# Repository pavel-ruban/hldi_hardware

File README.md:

# hldi_hardware

This is code for STM32f103 based PCB which implement home laser for home PCB manufacturing, it use ultra violet laser to make photoresis method done PCBs

Basically it's CNC machine which currently has 2 variants:
1. x axis stepper motor + y axis DC brushed motor with optical encoder line from PC printer
2. 2 axes are done with DC brushed motors kinematic is corexy 

Caution: This is currently in raw alpha & not fully working

GUI for this stuff can be found in sibling repository: https://github.com/pavel-ruban/hldi_gui

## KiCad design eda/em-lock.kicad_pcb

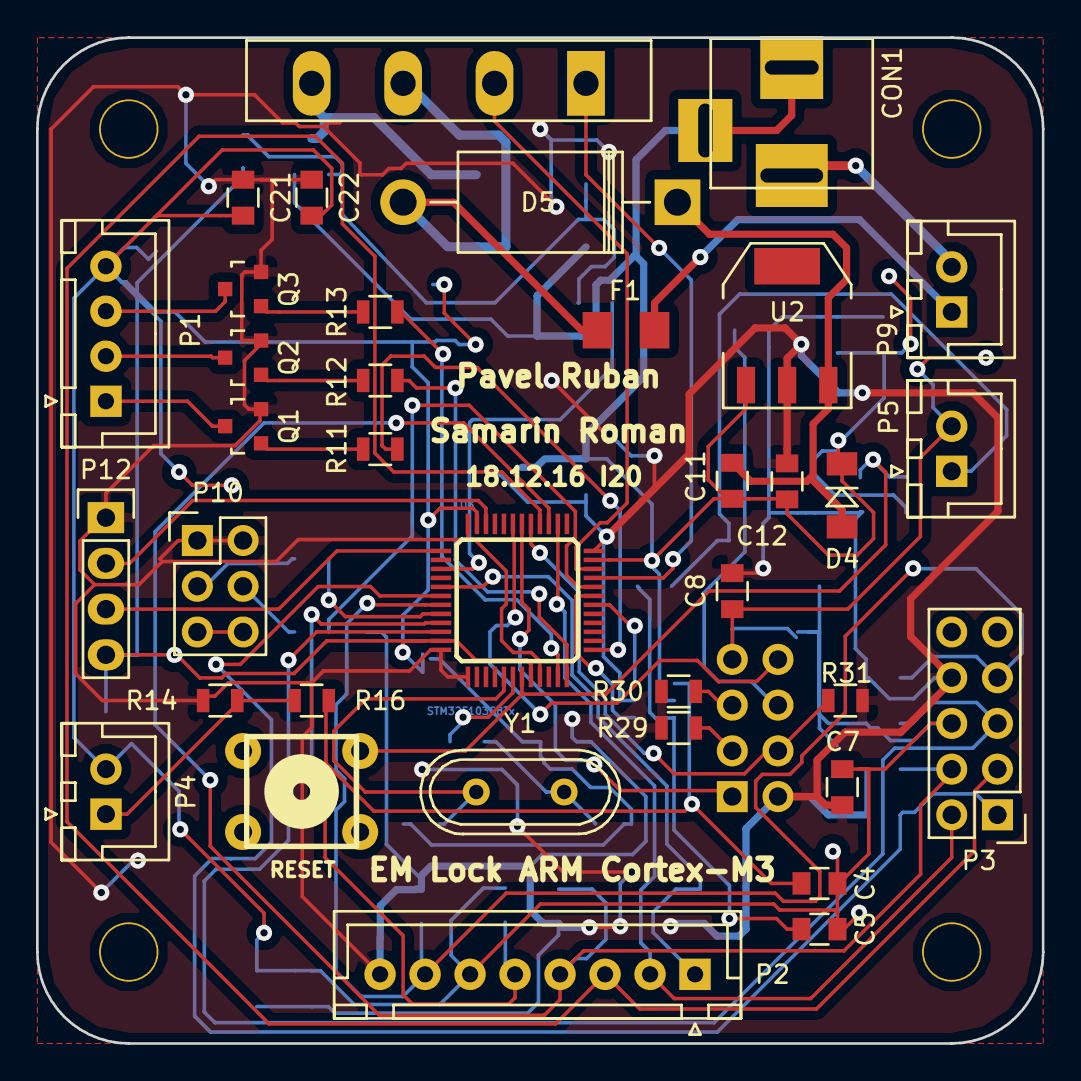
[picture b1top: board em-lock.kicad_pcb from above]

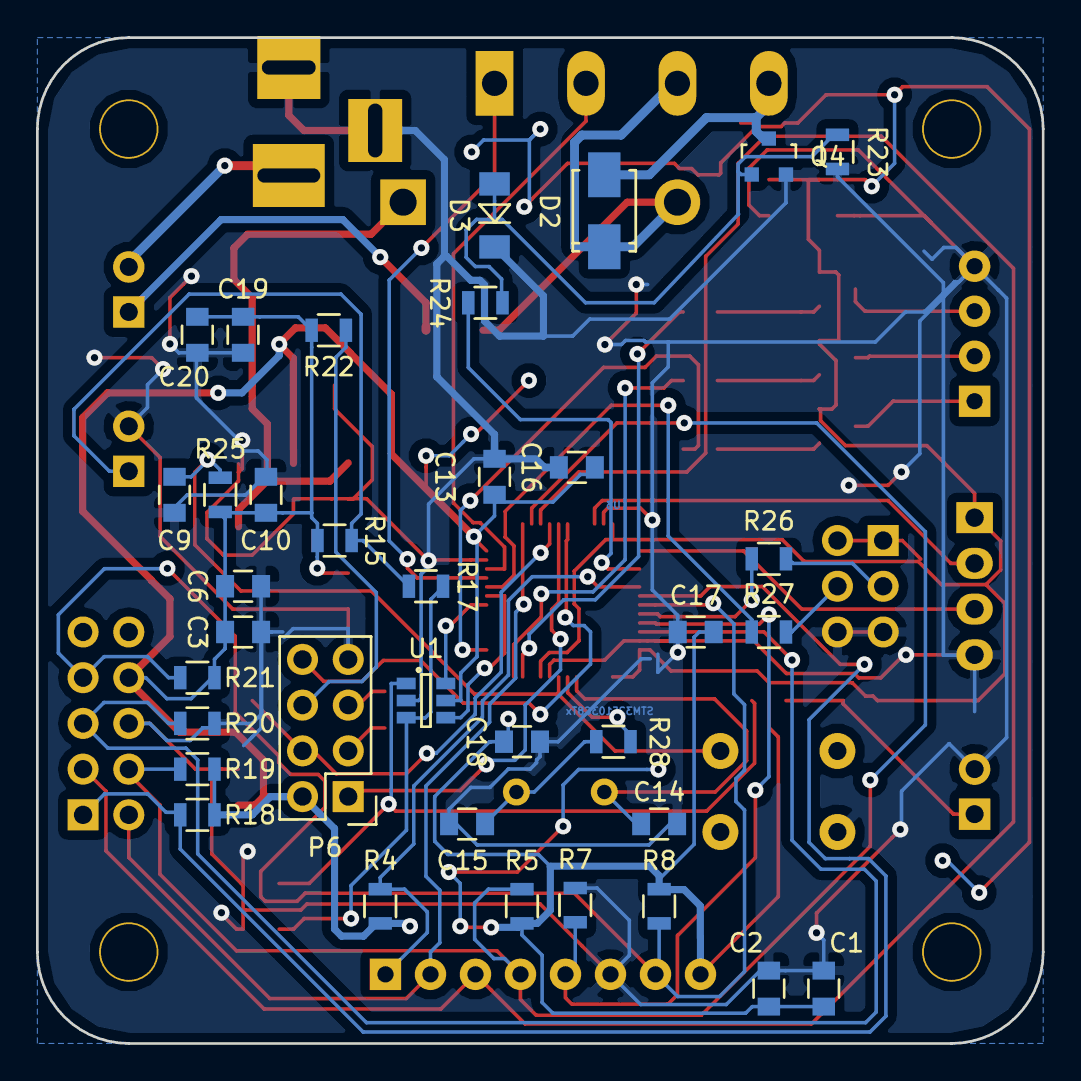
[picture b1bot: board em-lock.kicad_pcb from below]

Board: 2 copper layers, 55.9 x 55.9 mm, 78 parts (36 on the bottom side), 50 nets.

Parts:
C1, C3, C7, C9, C10, C13, C16, C17, C18, C22: 100nF; C_0805
C2, C6, C8, C11, C19, C21: 10uF; C_0805
C4, C5: 0; C_0805
C12: 22uF; C_0805
C14, C15: 2pF; C_0805
C20: 1uF; C_0805
CON1: BARREL_JACK; DC-005
D2: M7; SMA_Standard
D3: ZENER-MOSFET-GATE; MiniMELF_Standard
D4: LDO-12V; MiniMELF_Standard
D5: 0; Diode_DO-201AD_Horizontal_RM15
F1: 3A; Fuse_SMD1206_Wave
H1, H2, H3, H4: MountingHole_3.1mm
H8, H9: MountingHole_1.9mm
P1: EXT_LED_CONN; JST_XH_B04B-XH-A_04x2.50mm_Straight
P2: RC522A; JST_XH_B08B-XH-A_08x2.50mm_Straight
P3: RC522B; Pin_Header_Straight_2x05
P4: BTN_OPEN; JST_XH_B02B-XH-A_02x2.50mm_Straight
P5: BTN_CALL; JST_XH_B02B-XH-A_02x2.50mm_Straight
P6: ESP8266_CONN; ESP8266
P7: LOCK_CONN; PhoenixContact_MSTBA-G_04x5.08mm_Angled
P9: PWR_SW_CONN; JST_XH_B02B-XH-A_02x2.50mm_Straight
P10: BOOT_SEL_CONN; Pin_Header_Straight_2x03
P12: SWD_CONN; Pin_Header_Straight_1x04
Q1, Q2, Q3: MMBT3906; SOT-23
Q4: MOSFET-NCHANNELSMD; SOT-23
R4, R5, R7, R8, R18, R19, R20, R21, R22, R29, R30, R31: 4.7k; R_0805
R11, R12, R13: 2k; R_0805
R14, R15, R23, R25, R26, R27: 10k; R_0805
R16, R17: 0; R_0805
R24: 240; R_0805
R28: 0R; R_0805
RESET: RST_BTN; PCB_PUSH
U1: 74LVC2G14; SOT-23-6
U2: LD1117S33CTR; SOT-223
U3: STM32F103C8Tx; SparkFun-LQFP-48
Y1: 8MHz; Crystal_HC49-U_Vertical

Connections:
/stm32f103c8/12V_EXT: CON1.1, P9.2
/stm32f103c8/BOOT0: R26.1, U3.44
/stm32f103c8/LDO_IN: C11.1, D4.1, D5.1, U2.3
/stm32f103c8/NRST: C9.1, R25.1, RESET.2, U3.7
/stm32f103c8/PB2/BOOT1: R27.1, U3.20
/stm32f103c8/PD0/RCC_OSC_IN: C14.1, U3.5, Y1.1
/stm32f103c8/PD1/RCC_OSC_OUT: R28.1, U3.6
/stm32f103c8/SWCLK: P12.3, U3.37
/stm32f103c8/SWDIO: P12.2, U3.34
BTN_CALL: U1.4, U3.19
BTN_OPEN: U1.6, U3.18
EM_LOCK: D2.1, D5.2, F1.1, P7.3
ESP_RESET: P6.4, R31.2, U3.29
GND: C1.2, C2.2, C3.2, C4.1, C5.1, C6.2, C7.1, C8.1, C9.2, C10.2, C11.2, C12.2, C13.1, C14.2, C15.2, C16.2, C17.2, C18.2, C19.1, C20.1, C21.2, C22.2, CON1.2, CON1.3, D3.2, D4.2, P1.4, P2.6, P3.6, P4.2, P5.2, P6.7, P10.5, P10.6, P12.4, Q4.2, R7.1, R20.1, R23.2, RESET.1, U1.2, U2.1, U3.8, U3.23, U3.35, U3.47
LOCK_GND: D2.2, P7.4, Q4.3
LOCK_OPEN: R24.1, U3.39
unnamed: C4.2, R16.1, U1.1
unnamed: C5.2, R17.1, U1.3
unnamed: C15.1, R28.2, Y1.2
unnamed: D3.1, Q4.1, R23.1, R24.2
unnamed: F1.2, P9.1
unnamed: P4.1, R14.2, R16.2
unnamed: P5.1, R15.2, R17.2
unnamed: P6.3, R29.1
unnamed: P6.5, R30.1
unnamed: P6.6, R22.2
unnamed: P10.3, R26.2
unnamed: P10.4, R27.2
unnamed: Q1.1, R11.1
unnamed: Q2.1, R12.1
unnamed: Q3.1, R13.1
OUT_BLUE: P1.1, Q1.3
OUT_GREEN: P1.2, Q2.3
OUT_RED: P1.3, Q3.3
PB5_RC522A_CS: P2.1, R4.2, U3.41
PB6_RC522B_CS: P3.1, R18.2, U3.42
PB7_RC522_RST: P2.7, P3.7, R8.2, R21.2, U3.43
PB8_RC522A_IRQ: P2.5, R7.2, U3.45
PB9_RC522B_IRQ: P3.5, R20.2, U3.46
PB13_SPI2_SCK: P2.2, P3.2, U3.26
PB14_SPI2_MISO: P2.4, P3.4, R5.2, R19.2, U3.27
PB15_SPI2_MOSI: P2.3, P3.3, U3.28
PIN_BLUE: R11.2, U3.13
PIN_GREEN: R12.2, U3.12
PIN_RED: R13.2, U3.11
UART_EXT_RX: P7.2, U3.22
UART_EXT_TX: P7.1, U3.21
UART_INT_RX: P6.8, U3.31
UART_INT_TX: P6.1, U3.30
VCC: C1.1, C2.1, C3.1, C6.1, C7.2, C8.2, C10.1, C12.1, C13.2, C16.1, C17.1, C18.1, C19.2, C20.2, C21.1, C22.1, P2.8, P3.8, P6.2, P10.1, P10.2, P12.1, Q1.2, Q2.2, Q3.2, R4.1, R5.1, R8.1, R14.1, R15.1, R18.1, R19.1, R21.1, R22.1, R25.2, R29.2, R30.2, R31.1, U1.5, U2.2, U3.1, U3.9, U3.24, U3.36, U3.48

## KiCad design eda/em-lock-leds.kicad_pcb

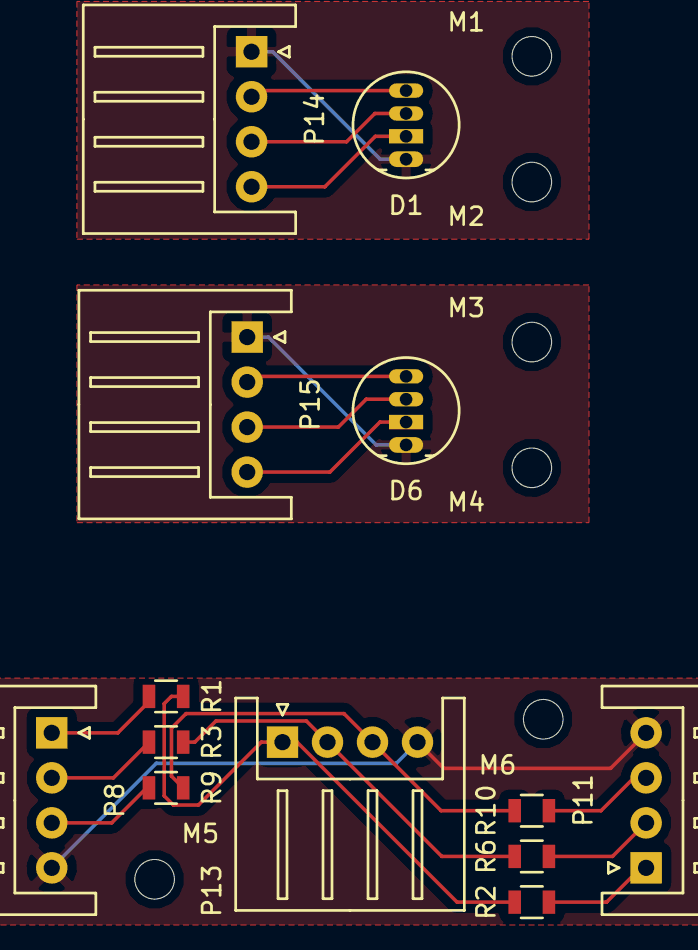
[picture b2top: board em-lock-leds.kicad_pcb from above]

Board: 2 copper layers, 21 parts (0 on the bottom side), 18 nets.

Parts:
D1, D6: LED_RCBG; LED-RGB-5MM_Common_Cathode
H8, H9: MountingHole_1.9mm
M1, M2, M3, M4, M5, M6: MountingHole_2.2mm_M2
P8, P14, P15: LEDB_CONN; JST_XH_S04B-XH-A_04x2.50mm_Angled
P11: LEDA_CONN; JST_XH_S04B-XH-A_04x2.50mm_Angled
P13: IN_LED_CONN; JST_XH_S04B-XH-A_04x2.50mm_Angled
R1, R2: 82R; R_0805
R3, R6: 15R; R_0805
R9, R10: 10R; R_0805

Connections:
unnamed: D1.1, P14.1
unnamed: D1.2, P14.4
unnamed: D1.3, P14.3
unnamed: D1.4, P14.2
unnamed: D6.1, P15.1
unnamed: D6.2, P15.4
unnamed: D6.3, P15.3
unnamed: D6.4, P15.2
unnamed: P8.1, R1.1
unnamed: P8.2, R3.1
unnamed: P8.3, R9.1
unnamed: P11.1, R2.1
unnamed: P11.2, R6.1
unnamed: P11.3, R10.1
unnamed: P8.4, P11.4, P13.4
unnamed: P13.1, R1.2, R2.2
unnamed: P13.2, R3.2, R6.2
unnamed: P13.3, R9.2, R10.2

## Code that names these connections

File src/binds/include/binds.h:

#pragma once
#pragma pack(1)

#include <stdint.h>

#include "spi_binds.h"
#include "ethernet_binds.h"
#include <stm32f10x_conf.h>

#define LED_INDICATOR_PORT GPIOA
#define LED_INDICATOR_PIN_RED GPIO_Pin_1
#define LED_INDICATOR_PIN_GREEN GPIO_Pin_2
#define LED_INDICATOR_PIN_BLUE GPIO_Pin_3
#define BTN_CALL_PORT GPIOB
#define BTN_CALL_PIN GPIO_Pin_1
#define BTN_OPEN_PORT GPIOB
#define BTN_OPEN_PIN GPIO_Pin_0
#define EM_LOCK_PORT GPIOB
#define EM_LOCK_PIN GPIO_Pin_3
#define ESP8266_RESET_PIN GPIO_Pin_8
#define ESP8266_RESET_PORT GPIOA


#ifdef __cplusplus
extern "C" {
#endif
extern volatile uint32_t ticks;
#ifdef __cplusplus
}
#endif

void *memcpy(void *s1, const void *s2, size_t n);
void *memset(void *dst, int val, size_t count);
size_t strlen(const char* str);
int strncmp(const char *str1, const char *str2, size_t len);
//void strcpy(char* str1, char* str2);

void __enable_enc28j60_irq();
void __disable_enc28j60_irq();

void Delay(vu32 nCount);

#pragma pack(1)

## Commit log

2016-08-22 add readme
2016-08-22 Init develop branch
2016-08-23 init em-lock
2016-08-23 Edited readme.md
2016-08-23 added led class
2016-08-24 cplusplus constructor fail
2016-08-24 add file
2016-08-24 updated from pavelruban/arm master
2016-08-24 led class base functionality
2016-08-24 Init commit
2016-08-24 OSC and power filtering caps added to schematics
2016-08-25 Project hierarhy changed
2016-09-12 refs #39165 hardfail stm32
2016-09-12 39165_feature hardfault fixed, refactoring
2016-09-13 38128_feature RGB_led finished, systick rework
2016-09-16 refs #38128 EXTI interrupts, r/a container, iterator w/o start/end
2016-09-19 refs #38128 sheduler, endless loop at container.
2016-09-20 refs #38128 container implemented, scheduler have .event problems, so broken.
2016-09-21 refs #38128 Templated event, array capacity fix
2016-09-23 refs #39600 machine state implemented, perifferals also mapped
2016-09-23 refs #39739 code refactored
2016-09-23 refs #39740 usart class for rx/tx implemented
2016-09-26 refs #39740 usart wifi module tests, still Rx problem
2016-09-27 refs #39740 Wifi module class implemented, requests reversed
2016-09-30 refs #39740 wifi module implemented but requests.
2016-10-06 refs #39740 send, recv methods implemented
2016-10-07 newlib, provide ability to use stdc library
2016-10-14 refs #39740 double mode_change fix, authorization implemented.
2016-10-29 add clib
2016-10-31 refs #41563 implemented kicad schematics stm32 hierarchical sheet.
2016-10-31 refs #41563 update kicad schematics stm32 hierarchical sheet.
2016-11-02 refs #41563 refined em-lock schematics, 2 spi rc522 devices added.
2016-11-02 refs #41563 fix stable schematics version
2016-11-02 refs #41563 pcb projecting half-done
2016-11-07 refs #41563 rc522 moved up, RGB LEDs moved to separate pcbs, 3d model of rc522 implemented.
2016-11-11 refs #41563 pcb update.
2016-11-11 refs #41563 pcb done (pochti ;))
2016-11-14 refs #41563 main pcb done, todo: leds pcb multiplexor
2016-11-14 refs #41563 +leds multiplexor + leds pcb's
2016-11-14 refs #40861 rc522 code half-scratched from other project.
2016-11-18 refs #40861 rc522 works, 1 module tested, todo: bind to server-wifi.
2016-11-21 refs #40861 wi-fi connection handler wrapped
2016-11-24 uart bug timings
2016-11-25 refs #40861 wi-fi to uart connection totally reworked.
2016-11-26 refs #40861 wi-fi module wrapped, code refactored, tested, added error handlers.
2016-11-30 refs #40861 on current code B3 pin still struggling, even in case do not touching him in endless loop
2016-11-30 refs #40861 updated, but still doesnot work. Waiting new chip.
2016-12-02 rc522 modules sending auth requests, and a bit of caching
2016-12-03 refs 40861 rc522 modules correcly binded to machine states, machine states also improved, priority implemented and tested (f.e: opening is highest, idle and networking is background, etc.
2016-12-09 refs #40863 caching added.
2016-12-16 refs #40863 rc522 cache dumping work
2016-12-18 fix PCB before manufacturing
2016-12-19 add new files
2016-12-19 refs #40863 caching improved
2016-12-27 refs #40863 additional states, tests
2016-12-30 refs #41563 GPIO ESP module connected to the VCC
2017-01-13 fix PCB problems
2017-01-13 add screenshot
2017-01-13 add manufacturing files
2017-01-23 refs #40863 uart priority updated. Seems like no more dropping packets. Epic win (probably)
2017-01-24 refs #40863 caching sync and dumping, tested. Dumping should be tested with lags.
2017-01-25 refs #40863 caching sync and dumping, also testing.
2017-01-26 refs #40863 jitter rc522 bug fix
2017-02-01 fix style errors
2017-02-03 protocol updated due bo changes
2017-02-06 refs 40863 card invalidation server-called implemented
2017-02-13 refs #40863 rc522 restart timer code added. A bit tested, seems fine
2017-02-14 refs #40863 some connection fixes and crunches
2017-02-14 fix problem
2017-02-14 refs #40863 a bit more esp fixes
2017-02-14 refs #40863 ESP8266 responce collision fixed, bug appeared after morning status invalidation feature
2017-02-14 refs #40863 tests bf
2017-02-14 refs #40864 rc522 timer fixes
2017-02-16 refs #40863 1-line prev. state fix
2017-03-07 refs #40863 pcb tests
2017-03-08 refs #40863 both rc522 connected to p.dev and tested. Theyre working
2017-03-20 Revert "Merge branch 'develop'"
    This reverts commit ff1c94cd9af79a798b971b643cbdc9d823101f0c, reversing
    changes made to 75416340a58c0ce3ae2d4917c1e5600380b4c8a3.
2017-03-20 align with recent develop changes
2017-03-20 format code
2017-03-20 reformat code, fix hard fault exception for uart queue handler which was caused by wrong irq execution while class was not initialized yet
2017-07-23 fast clean old project
2017-07-23 implement servo interface for controling DC brushed motor, use UART as common communication protocol
2017-07-23 clean old garbage off
2017-07-23 quadrature encoder implementation start
2017-07-30 implementing PID regulator
2017-08-06 position PID adjustments, testing
